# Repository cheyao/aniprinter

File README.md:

# The Aniprinter

The ani* series printer! The custom aniprinter!

Are you restricted by your bed size, but don't have a lot of money to upgrade? This printer is for you! (No cap :3)

Aniprinter is cheap and big! You get a 310x310mm bed with only 150$!

(Yes, I know I used the full 300$ grant, but that's because I had to take shipping by air >.<)

## BOM

Check the `JOURNAL.md` for a BOM! Paired with taobao links.

## Nichies

This printer will have removable cat ears with magnets!

It uses a 300W PSU. Be carful not to get shocked.

The nozzle design is optimized for maximal airflow.

The X axis uses linear rods to move. The Y axis a linear rail and the Z axis two lead screws paired with linear rods.

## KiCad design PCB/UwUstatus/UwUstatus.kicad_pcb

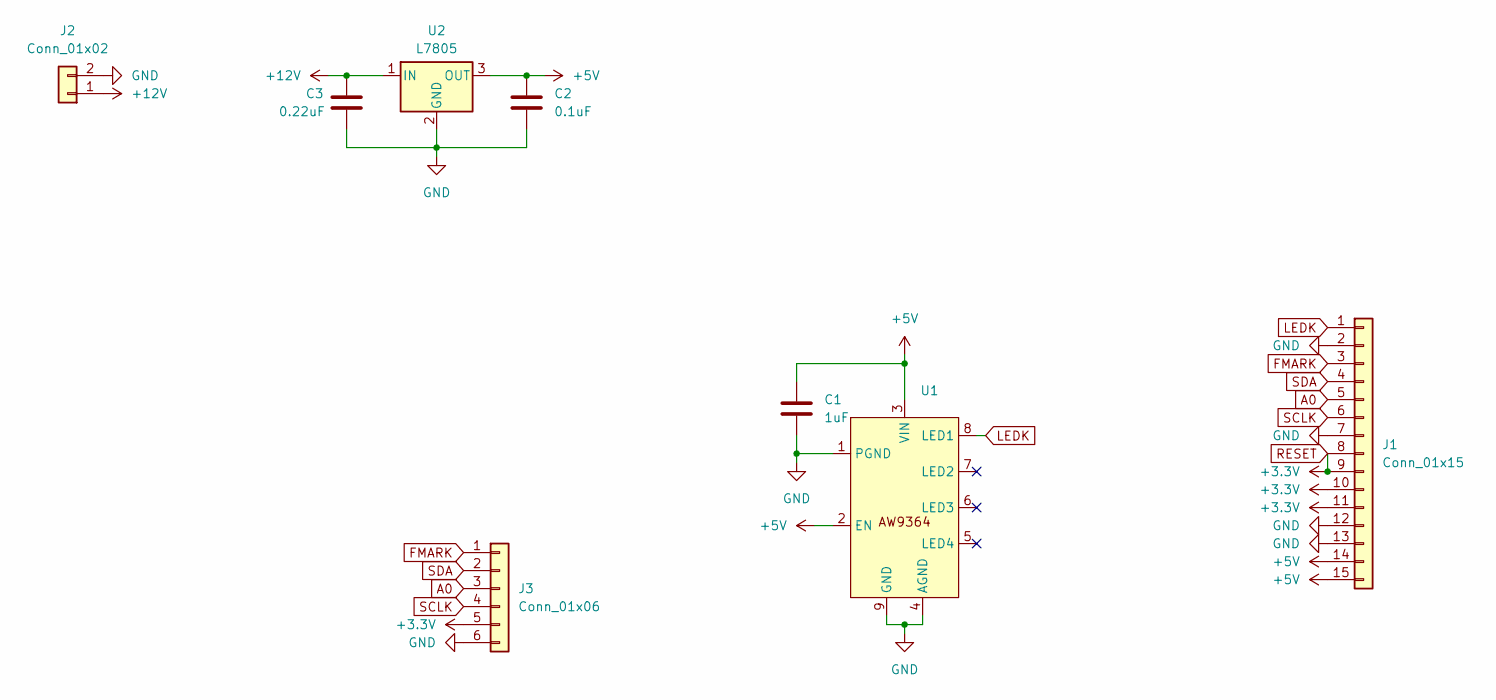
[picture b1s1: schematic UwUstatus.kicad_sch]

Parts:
C1: 1uF; C_0805_2012Metric_Pad1.18x1.45mm_HandSolder
C2: 0.1uF; C_0805_2012Metric_Pad1.18x1.45mm_HandSolder
C3: 0.22uF; C_0805_2012Metric_Pad1.18x1.45mm_HandSolder
J1: Conn_01x15; Hirose_FH26-15S-0.3SHW_2Rows-15Pins-1MP_P0.60mm_Horizontal
J2: Conn_01x02; TerminalBlock_Phoenix_MKDS-1,5-2-5.08_1x02_P5.08mm_Horizont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
J3: Conn_01x06; PinHeader_1x06_P2.54mm_Vertical
U1: DFN-8-1EP_2x2mm_P0.5mm_EP0.6x1.2mm
U2: L7805; SOT-223-3_TabPin2

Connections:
+5V: C1.1, C2.1, J1.14, J1.15, U1.2 (EN), U1.3 (VIN), U2.3 (OUT)
+12V: C3.1, J2.1, U2.1 (IN)
A0: J1.5, J3.3
FMARK: J1.3, J3.1
GND: C1.2, C2.2, C3.2, J1.2, J1.7, J1.12, J1.13, J2.2, J3.6, U1.1 (PGND), U1.4 (AGND), U1.9 (GND), U2.2 (GND)
LEDK: J1.1, U1.8 (LED1)
RESET: J1.8, J1.9, J1.10, J1.11, J3.5
SCLK: J1.6, J3.4
SDA: J1.4, J3.2

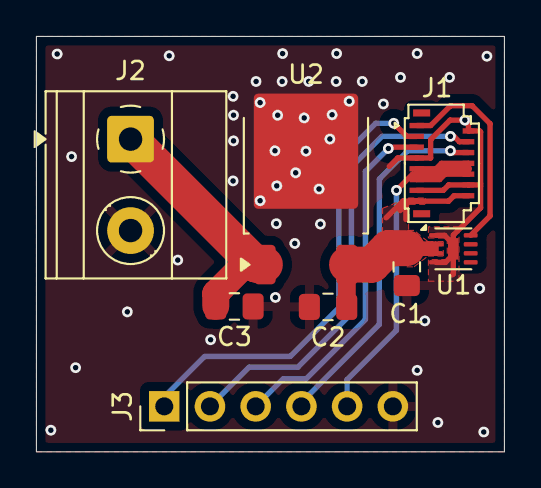
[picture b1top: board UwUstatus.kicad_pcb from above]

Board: 2 copper layers, 26.0 x 23.1 mm, 8 parts (0 on the bottom side), 9 nets.

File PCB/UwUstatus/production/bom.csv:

Designator,Footprint,Quantity,Value,LCSC Part #
C1,0805,1,1uF,
C2,0805,1,0.1uF,
C3,0805,1,0.22uF,
J1,Hirose_FH26-15S-0.3SHW_2Rows-15Pins-1MP_P0.60mm_Horizontal,1,Conn_01x15,
J2,"TerminalBlock_Phoenix_MKDS-1,5-2-5.08_1x02_P5.08mm_Horizontal",1,Conn_01x02,
J3,PinHeader_1x06_P2.54mm_Vertical,1,Conn_01x06,
U1,DFN-8-1EP_2x2mm_P0.5mm_EP0.6x1.2mm,1,~,
U2,TO-252-2,1,L7805,

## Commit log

2025-02-02 Init
2025-02-02 Add a time table
2025-02-03 Some more work
2025-02-03 Define requirements
2025-02-06 More work
2025-02-16 Work!
2025-02-17 Workie
2025-02-20 Save
2025-02-21 Finish bottom
2025-02-21 Add pic
2025-02-22 All axis
2025-02-23 Hotend assembly
2025-02-24 work
2025-03-02 Base Done!
2025-03-02 Add hour!
2025-03-03 Add screws!
2025-03-04 Finish?
2025-03-23 Update journal
2025-03-25 Remove undeeded thing
2025-03-27 Log!
2025-04-02 Add time spent ordering stuff
2025-04-04 Final revision
2025-04-21 Add a bit of info to the README
